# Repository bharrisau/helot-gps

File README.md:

helot-gps
=======

GPS addin board for Helot development platform.

## License

Copyright 2013 Ben Harris
Copyright and related rights are licensed under the Solderpad Hardware License, Version 0.51 (the “License”); you may not use this file except in compliance with the License. You may obtain a copy of the License at http://solderpad.org/licenses/SHL-0.51. Unless required by applicable law or agreed to in writing, software, hardware and materials distributed under this License is distributed on an “AS IS” BASIS, WITHOUT WARRANTIES OR CONDITIONS OF ANY KIND, either express or implied. See the License for the specific language governing permissions and limitations under the License.

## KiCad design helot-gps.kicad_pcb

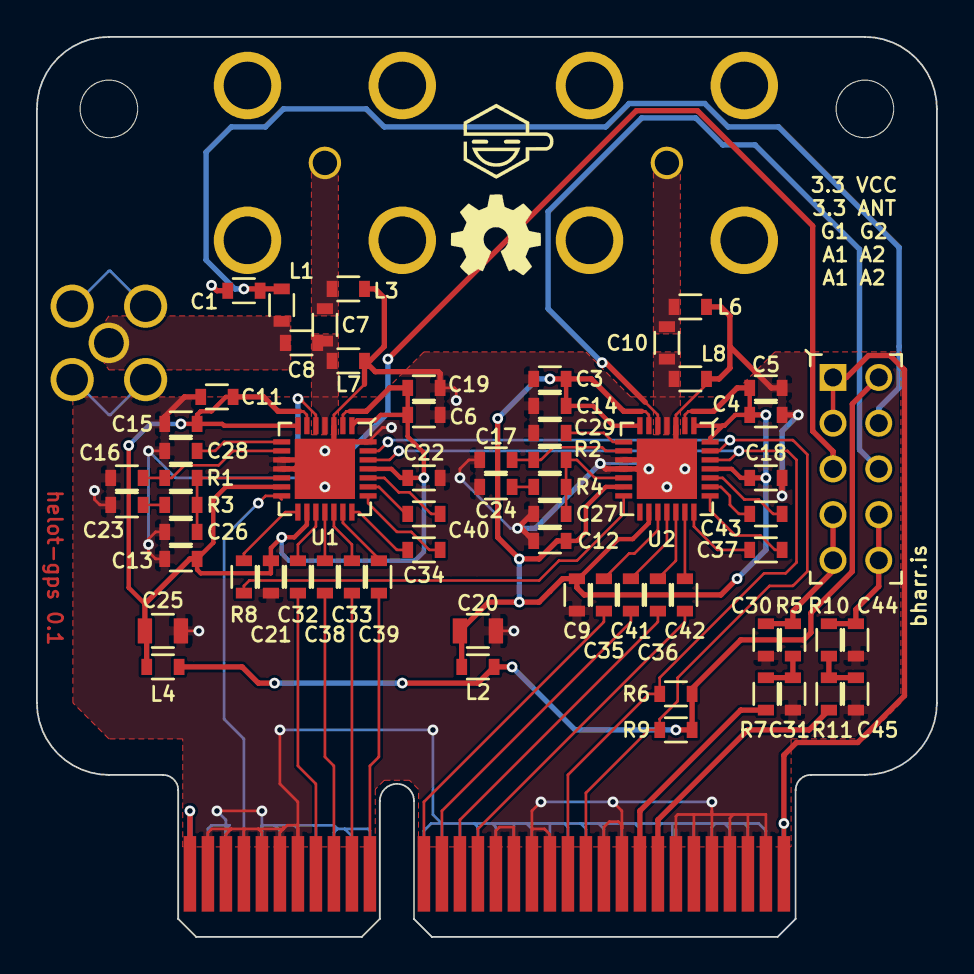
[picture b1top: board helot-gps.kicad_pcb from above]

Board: 2 copper layers, 50.0 x 50.0 mm, 71 parts (0 on the bottom side), 57 nets.

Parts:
C1, C3, C4, C5, C6, C9, C11, C12, C13, C14, C15, C18, C19, C21, C22, C28, C29, C30, C31, C44, C45: 1u; CAPC1608N
C7, C8: 2.2p; CAPC1608N
C10: 0R; CAPC1608N
C16, C17: 100p; CAPC1608N
C20, C25: 22u; CAPC2012N
C23, C24: 33n; CAPC1608N
C26, C27: 2.2n; CAPC1608N
C32, C33, C34, C35, C36, C37, C38, C39, C40, C41, C42, C43: 47n; CAPC1608N
HOLE_M3, HOLE_M3#2: Val**; HOLE_M3
L1: 33n; INDC1608N
L2, L4: FBlow; INDC1608N
L3: 22n; INDC1608N
L6, L8: NC; INDC1608N
L7: 10n/22n; INDC1608N
P1: SMA_1; TE_1814832
P2: FCONN_1; MOLEX_7330_0030
P3: FCONN_2; MOLEX_7330_0030
P4: HELOT_PCIE
P5: HEADER; HEADER254P2X5
R1, R2: 820; RESC1608N
R3, R4: 390; RESC1608N
R5, R7, R10, R11: 100k; RESC1608N
R6, R9: 1k; RESC1608N
R8: 33; RESC1608N
U1, U2: MAX2112

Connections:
/3.3V: P4.63, P4.64, P5.1, P5.3
/50R_1: C8.1, L1.2, P1.1
/75R_1: C7.1, L3.2, P2.1
/75R_2: C7.2, C8.2, L7.2, U1.4
/75R_3: C10.1, L6.2, P3.1
/75R_4: C10.2, L8.2, U2.4
/ANT_PWR: C1.2, L1.1, P5.4
/CLK: P4.8, U1.14
/CLK_2: R8.2, U2.14
/DAC1: C30.1, P5.7, P5.9, R5.1
/DAC2: C44.1, P5.8, P5.10, R10.1
/DP1: P4.47, R7.2
/DP2: P4.49, R11.2
/GC1: P5.5, U1.5
/GC2: P5.6, U2.5
/SCL: P4.41, R9.1, U1.27, U2.27
/SDA: P4.39, R6.1, U1.26, U2.26
/VCC: L2.1, L4.1, P5.2, R6.2, R9.2
/VCC1: C6.1, C11.1, C13.1, C15.1, C19.1, C21.1, C22.1, C25.1, L4.2, U1.1, U1.2, U1.6, U1.7, U1.13, U1.16, U1.25
/VCC2: C3.1, C4.1, C5.1, C9.1, C12.1, C14.1, C18.1, C20.1, L2.2, U2.1, U2.2, U2.6, U2.7, U2.13, U2.16, U2.25, U2.28
GND: C1.1, C3.2, C4.2, C5.2, C6.2, C9.2, C11.2, C12.2, C13.2, C14.2, C15.2, C16.2, C17.2, C18.2, C19.2, C20.2, C21.2, C22.2, C23.2, C24.2, C25.2, C26.2, C27.2, C28.2, C29.2, C30.2, C31.2, C44.2, C45.2, L3.1, L6.1, L7.1, L8.1, P1.2, P2.2, P3.2, P4.3, P4.4, P4.5, P4.6, P4.7, P4.9, P4.10, P4.11, P4.12, P4.13, P4.14, P4.16, P4.18, P4.20, P4.22, P4.24, P4.26, P4.28, P4.30, P4.31, P4.32, P4.33, P4.34, P4.35, P4.36, P4.37, P4.38, P4.40, P4.42, P4.43, P4.44, P4.45, P4.46, P4.48, P4.50, P4.51, P4.52, P4.53, P4.54, P4.55, P4.56, P4.57, P4.58, P4.59, P4.60, P4.61, P4.62, U1.3, U1.10, U1.11, U1.28, U1.29, U2.3, U2.10, U2.11, U2.29
unnamed: C42.2, P4.29
unnamed: C36.2, P4.27
unnamed: C41.2, P4.25
unnamed: C35.2, P4.23
unnamed: P4.1, P4.2
unnamed: C45.1, R10.2, R11.1
unnamed: R8.1, U1.15
unnamed: C31.1, R5.2, R7.1
unnamed: C37.2, U2.22
unnamed: C35.1, U2.17
unnamed: C36.1, U2.19
unnamed: C37.1, U2.21
unnamed: C43.1, U2.23
unnamed: C43.2, U2.24
unnamed: C42.1, U2.20
unnamed: C41.1, U2.18
unnamed: C27.1, R2.2, R4.1, U2.12
unnamed: C24.1, R4.2
unnamed: C29.1, U2.8
unnamed: C17.1, R2.1, U2.9
unnamed: C39.2, P4.21
unnamed: C33.2, P4.19
unnamed: C38.2, P4.17
unnamed: C32.2, P4.15
unnamed: C16.1, R1.1, U1.9
unnamed: C34.2, U1.22
unnamed: C40.1, U1.23
unnamed: C39.1, U1.20
unnamed: C34.1, U1.21
unnamed: C26.1, R1.2, R3.1, U1.12
unnamed: C23.1, R3.2
unnamed: C40.2, U1.24
unnamed: C32.1, U1.17
unnamed: C38.1, U1.18
unnamed: C33.1, U1.19
unnamed: C28.1, U1.8

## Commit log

2013-08-25 working
2013-08-25 licence
2013-09-11 routing (need to fix edge connector footprint)
2013-09-12 routing
2013-09-12 some simple stuff done (just saving my progress)
2013-09-12 one more
2013-09-13 need to clear some area around the rf traces
